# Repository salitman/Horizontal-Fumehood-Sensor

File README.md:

# Horizontal-Fumehood-Sensor
 Mounted device for detecting openness of a multi-panel sash fume hood

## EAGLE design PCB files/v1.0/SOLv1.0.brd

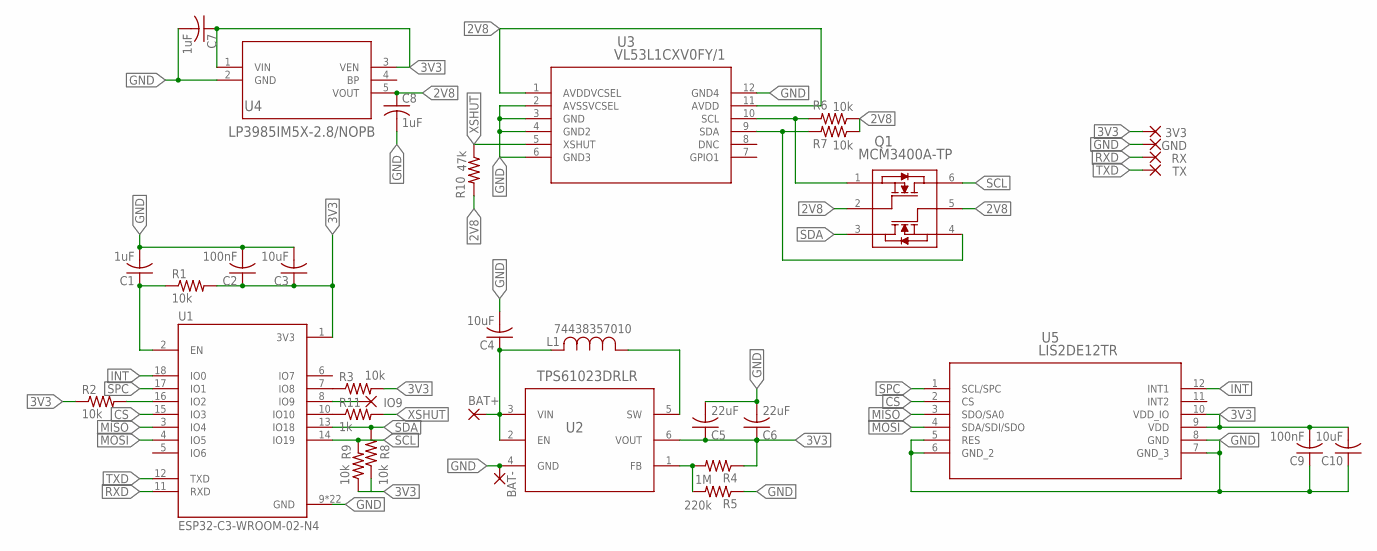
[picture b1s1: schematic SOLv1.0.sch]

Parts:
3V3: 1,6/0,8
BAT+: 1,6/0,8
BAT-: 1,6/0,8
C1, C7, C8: 1uF; C0805
C2, C9: 100nF; C0805
C3, C4, C10: 10uF; C0805
C5, C6: 22uF; C0805
GND: 1,6/0,8
IO9: 1,6/0,8
L1: 74438357010; IND_74438357010_WRE
Q1: MCM3400A-TP; DFN2020-6L_MCE
R1, R2, R3, R6, R7, R8, R9: 10k; R0805
R4: 1M; R0805
R5: 220k; R0805
R10: 47k; R0805
R11: 1k; R0805
RX: 1,6/0,8
TX: 1,6/0,8
U1: ESP32-C3-WROOM-02-N4; MODULE_ESP32-C3-WROOM-02-H4
U2: TPS61023DRLR; DRL0006A
U3: VL53L1CXV0FY/1; LGA12_STM
U4: LP3985IM5X-2.8/NOPB; MF05A
U5: LIS2DE12TR; LGA-12_STM

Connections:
2V8: C8.1, Q1.2, Q1.5, R6.1, R7.1, R10.2, U3.1 (AVDDVCSEL), U3.11 (AVDD), U4.5 (VOUT)
3V3: 3V3.1, C2.1, C3.1, C5.1, C6.1, C7.1, C9.2, C10.2, R1.2, R2.1, R3.2, R4.1, R8.1, R9.1, U1.1 (3V3), U2.6 (VOUT), U4.1 (VIN), U4.3 (VEN), U5.9 (VDD), U5.10 (VDD_IO)
CS: U1.15 (IO3), U5.2 (CS)
GND: BAT-.1, C1.2, C2.2, C3.2, C4.2, C5.2, C6.2, C7.2, C8.2, C9.1, C10.1, GND.1, R5.1, U1.9 (GND), U1.19 (GND), U1.20 (GND), U1.21 (GND), U1.22 (GND), U1.23 (GND), U1.24 (GND), U1.25 (GND), U1.26 (GND), U1.27 (GND), U1.28 (GND), U1.29 (GND), U1.30 (GND), U1.31 (GND), U1.32 (GND), U1.33 (GND), U1.34 (GND), U1.35 (GND), U1.36 (GND), U1.37 (GND), U1.38 (GND), U1.39 (GND), U2.4 (GND), U3.2 (AVSSVCSEL), U3.3 (GND), U3.4 (GND2), U3.6 (GND3), U3.12 (GND4), U4.2 (GND), U5.5 (RES), U5.6 (GND_2), U5.7 (GND_3), U5.8 (GND)
INT: U1.18 (IO0), U5.12 (INT1)
MISO: U1.3 (IO4), U5.3 (SDO/SA0)
MOSI: U1.4 (IO5), U5.4 (SDA/SDI/SDO)
unnamed: R2.2, U1.16 (IO2)
unnamed: C1.1, R1.1, U1.2 (EN)
unnamed: R3.1, U1.7 (IO8)
unnamed: IO9.1, U1.8 (IO9)
unnamed: BAT+.1, C4.1, L1.2, U2.2 (EN), U2.3 (VIN)
unnamed: L1.1, U2.5 (SW)
unnamed: R4.2, R5.2, U2.1 (FB)
unnamed: Q1.4, R7.2, U3.9 (SDA)
unnamed: R11.1, U1.10 (IO10)
unnamed: Q1.1, R6.2, U3.10 (SCL)
RXD: RX.1, U1.11 (RXD)
SCL: Q1.6, R9.2, U1.14 (IO19)
SDA: Q1.3, R8.2, U1.13 (IO18)
SPC: U1.17 (IO1), U5.1 (SCL/SPC)
TXD: TX.1, U1.12 (TXD)
XSHUT: R10.1, R11.2, U3.5 (XSHUT)

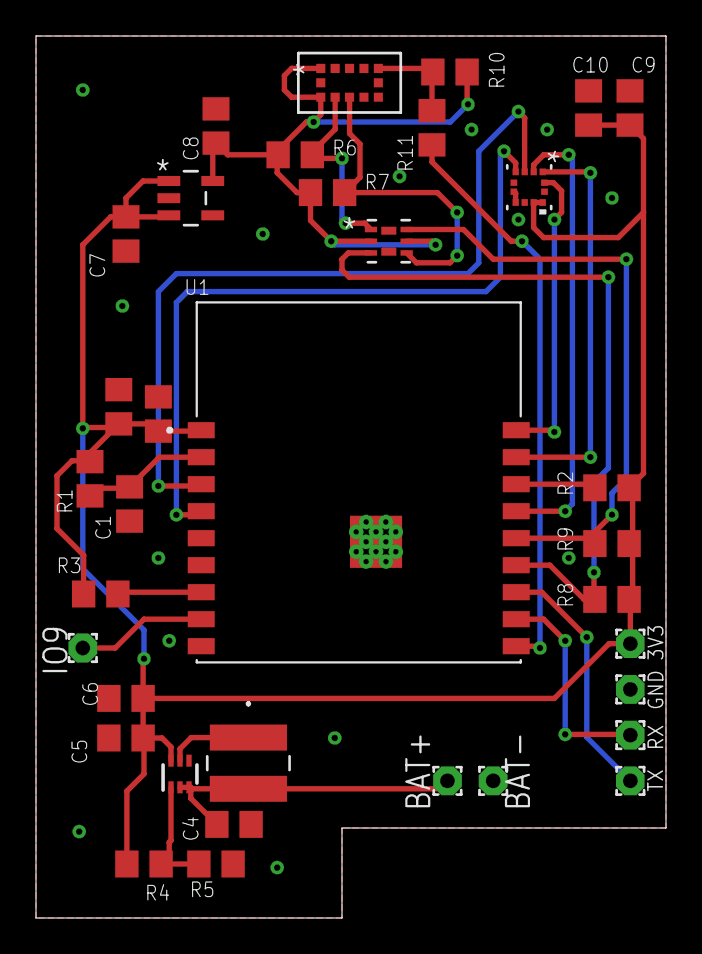
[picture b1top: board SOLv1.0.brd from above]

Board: 2 copper layers, 35.0 x 49.0 mm, 35 parts (0 on the bottom side), 23 nets.

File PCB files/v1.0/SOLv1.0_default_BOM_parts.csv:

"Part";"Value";"Device";"Package";"Library";"Description";"AVAILABILITY";"CHECK_PRICES";"COPYRIGHT";"DESCRIPTION";"MANUFACTURER_PART_NUMBER";"MF";"MFR_NAME";"MP";"PACKAGE";"POPULARITY";"PRICE";"REFDES";"SNAPEDA_LINK";"SPICEPREFIX";"TYPE";
"3V3";"";"1,6/0,8";"1,6/0,8";"wirepad";"THROUGH-HOLE PAD";"";"";"";"";"";"";"";"";"";"15";"";"";"";"";"";
"BAT+";"";"1,6/0,8";"1,6/0,8";"wirepad";"THROUGH-HOLE PAD";"";"";"";"";"";"";"";"";"";"15";"";"";"";"";"";
"BAT-";"";"1,6/0,8";"1,6/0,8";"wirepad";"THROUGH-HOLE PAD";"";"";"";"";"";"";"";"";"";"15";"";"";"";"";"";
"C1";"1uF";"C-USC0805";"C0805";"rcl";"CAPACITOR, American symbol";"";"";"";"";"";"";"";"";"";"63";"";"";"";"C";"";
"C2";"100nF";"C-USC0805";"C0805";"rcl";"CAPACITOR, American symbol";"";"";"";"";"";"";"";"";"";"63";"";"";"";"C";"";
"C3";"10uF";"C-USC0805";"C0805";"rcl";"CAPACITOR, American symbol";"";"";"";"";"";"";"";"";"";"63";"";"";"";"C";"";
"C4";"10uF";"C-USC0805";"C0805";"rcl";"CAPACITOR, American symbol";"";"";"";"";"";"";"";"";"";"63";"";"";"";"C";"";
"C5";"22uF";"C-USC0805";"C0805";"rcl";"CAPACITOR, American symbol";"";"";"";"";"";"";"";"";"";"63";"";"";"";"C";"";
"C6";"22uF";"C-USC0805";"C0805";"rcl";"CAPACITOR, American symbol";"";"";"";"";"";"";"";"";"";"63";"";"";"";"C";"";
"C7";"1uF";"C-USC0805";"C0805";"rcl";"CAPACITOR, American symbol";"";"";"";"";"";"";"";"";"";"63";"";"";"";"C";"";
"C8";"1uF";"C-USC0805";"C0805";"rcl";"CAPACITOR, American symbol";"";"";"";"";"";"";"";"";"";"63";"";"";"";"C";"";
"C9";"100nF";"C-USC0805";"C0805";"rcl";"CAPACITOR, American symbol";"";"";"";"";"";"";"";"";"";"63";"";"";"";"C";"";
"C10";"10uF";"C-USC0805";"C0805";"rcl";"CAPACITOR, American symbol";"";"";"";"";"";"";"";"";"";"63";"";"";"";"C";"";
"GND";"";"1,6/0,8";"1,6/0,8";"wirepad";"THROUGH-HOLE PAD";"";"";"";"";"";"";"";"";"";"15";"";"";"";"";"";
"IO9";"";"1,6/0,8";"1,6/0,8";"wirepad";"THROUGH-HOLE PAD";"";"";"";"";"";"";"";"";"";"15";"";"";"";"";"";
"L1";"74438357010";"74438357010";"IND_74438357010_WRE";"74438357010";"";"";"";"Copyright (C) 2024 Ultra Librarian. All rights reserved.";"";"74438357010";"";"Wurth Electronics";"";"";"";"";"";"";"";"";
"Q1";"MCM3400A-TP";"MCM3400A-TP";"DFN2020-6L_MCE";"MCM3400A-TP";"";"";"";"Copyright (C) 2024 Ultra Librarian. All rights reserved.";"";"MCM3400A-TP";"";"MCC";"";"";"";"";"";"";"";"Transistors";
"R1";"10k";"R-US_R0805";"R0805";"rcl";"RESISTOR, American symbol";"";"";"";"";"";"";"";"";"";"85";"";"";"";"R";"";
"R2";"10k";"R-US_R0805";"R0805";"rcl";"RESISTOR, American symbol";"";"";"";"";"";"";"";"";"";"85";"";"";"";"R";"";
"R3";"10k";"R-US_R0805";"R0805";"rcl";"RESISTOR, American symbol";"";"";"";"";"";"";"";"";"";"85";"";"";"";"R";"";
"R4";"1M";"R-US_R0805";"R0805";"rcl";"RESISTOR, American symbol";"";"";"";"";"";"";"";"";"";"85";"";"";"";"R";"";
"R5";"220k";"R-US_R0805";"R0805";"rcl";"RESISTOR, American symbol";"";"";"";"";"";"";"";"";"";"85";"";"";"";"R";"";
"R6";"10k";"R-US_R0805";"R0805";"rcl";"RESISTOR, American symbol";"";"";"";"";"";"";"";"";"";"85";"";"";"";"R";"";
"R7";"10k";"R-US_R0805";"R0805";"rcl";"RESISTOR, American symbol";"";"";"";"";"";"";"";"";"";"85";"";"";"";"R";"";
"R8";"10k";"R-US_R0805";"R0805";"rcl";"RESISTOR, American symbol";"";"";"";"";"";"";"";"";"";"85";"";"";"";"R";"";
"R9";"10k";"R-US_R0805";"R0805";"rcl";"RESISTOR, American symbol";"";"";"";"";"";"";"";"";"";"85";"";"";"";"R";"";
"R10";"47k";"R-US_R0805";"R0805";"rcl";"RESISTOR, American symbol";"";"";"";"";"";"";"";"";"";"85";"";"";"";"R";"";
"R11";"1k";"R-US_R0805";"R0805";"rcl";"RESISTOR, American symbol";"";"";"";"";"";"";"";"";"";"85";"";"";"";"R";"";
"RX";"";"1,6/0,8";"1,6/0,8";"wirepad";"THROUGH-HOLE PAD";"";"";"";"";"";"";"";"";"";"15";"";"";"";"";"";
"TX";"";"1,6/0,8";"1,6/0,8";"wirepad";"THROUGH-HOLE PAD";"";"";"";"";"";"";"";"";"";"15";"";"";"";"";"";
"U1";"ESP32-C3-WROOM-02-N4";"ESP32-C3-WROOM-02-N4";"MODULE_ESP32-C3-WROOM-02-H4";"ESP32-C3-WROOM-02-N4";"WiFi Modules (802.11) (Engineering Samples) SMD module, ESP32-C3, 4MB SPI flash, PCB antenna, -40 C +105 C   Check availability  Check availability";"In Stock";"https://www.snapeda.com/parts/ESP32-C3-WROOM-02-N4/Espressif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";"";" WiFi Modules (802.11) (Engineering Samples) SMD module, ESP32-C3, 4MB SPI flash, PCB antenna, -40 C +85 C ";"";"Espressif Systems";"";"ESP32-C3-WROOM-02-N4";"Package ";"";"None";"";"https://www.snapeda.com/parts/ESP32-C3-WROOM-02-N4/Espressif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";"";"";
"U2";"TPS61023DRLR";"TPS61023DRLR";"DRL0006A";"TPS61023";"";"";"";"Copyright (C) 2024 Ultra Librarian. All rights reserved.";"";"TPS61023DRLR";"";"Texas Instruments";"";"";"";"";"RefDes";"";"";"TYPE";
"U3";"VL53L1CXV0FY/1";"VL53L1CXV0FY/1";"LGA12_STM";"VL53L1X";"";"";"";"Copyright (C) 2024 Ultra Librarian. All rights reserved.";"";"VL53L1CXV0FY/1";"";"STMicroelectronics";"";"";"";"";"";"";"";"";
"U4";"LP3985IM5X-2.8/NOPB";"LP3985IM5X-2.8/NOPB";"MF05A";"LP3985IM5X-2.8";"";"";"";"Copyright (C) 2024 Ultra Librarian. All rights reserved.";"";"LP3985IM5X-2.8/NOPB";"";"Texas Instruments";"";"";"";"";"";"";"";"LP3985IM5-2.5";
"U5";"LIS2DE12TR";"LIS2DE12TR";"LGA-12_STM";"LIS2DE12TR";"";"";"";"Copyright (C) 2024 Ultra Librarian. All rights reserved.";"";"LIS2DE12TR";"";"STMicroelectronics";"";"";"";"";"";"";"";"";

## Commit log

2025-05-26 First commit
    Adding sender and receiver code
    Receiver still records on SD card here
2025-05-27 Updates to sender and receiver code
    Added error handling / reporting from senders, root cause is mainly accelerometer
    Changed receiver to basic Serial for logging
    Split accelerometer functions to separate ino file
    Changed interrupt to high Y only (corresponds to horizontal axis once mounted)
2025-05-27 Adding original PCB files
    Adding PCB files for the sender module to repo

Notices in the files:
parts and their libraries:
COPYRIGHT: Copyright (C) 2024 Ultra Librarian. All rights reserved.
